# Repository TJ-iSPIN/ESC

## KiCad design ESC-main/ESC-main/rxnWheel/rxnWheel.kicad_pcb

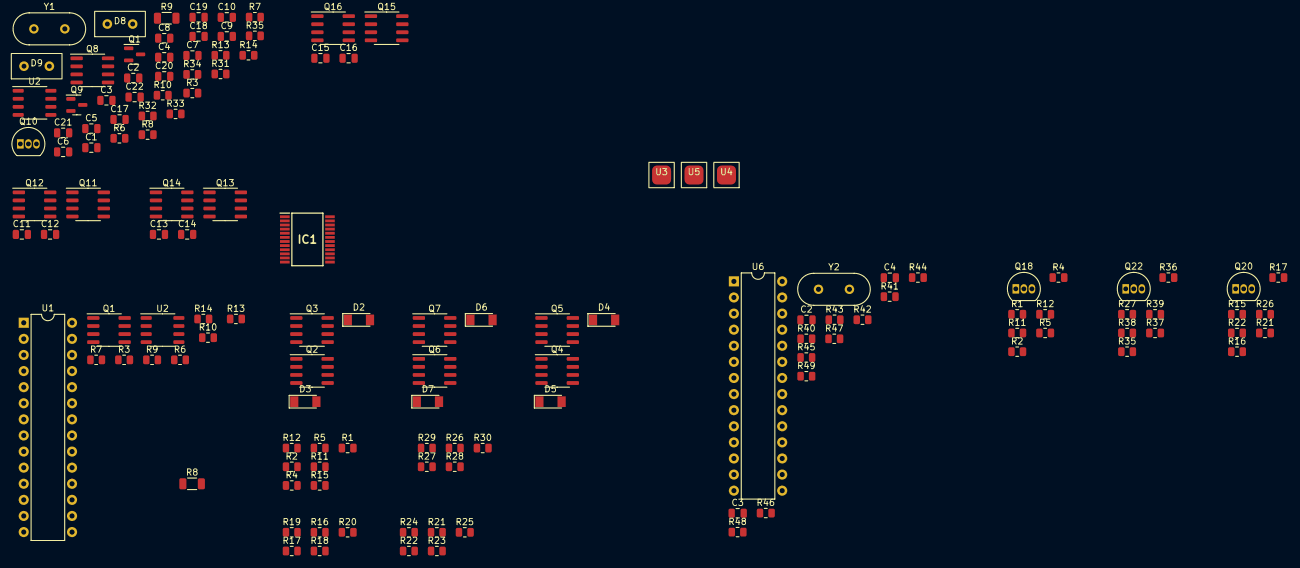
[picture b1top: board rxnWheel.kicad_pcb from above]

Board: 2 copper layers, 134 parts (0 on the bottom side), 73 nets, no tracks yet.

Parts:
C1, C3, C4#2, C8, C9, C10, C20, C21, C22: 1uF; C_0805_2012Metric
C2: 1nF; C_0805_2012Metric
C2#2, C3#2, C17, C18: 20pF; C_0805_2012Metric
C4: 0.47 uF; C_0805_2012Metric
C5, C7, C19: 0.1uF; C_0805_2012Metric
C6, C11, C12, C13, C14, C15, C16: 0.01uF; C_0805_2012Metric
D2, D3, D4, D5, D6, D7: BZV55B12; D_MiniMELF
D8: BPW20RF; 2x_jumper
D9: LED; 2x_jumper
IC1: TB9061AFNG; SOP65P760X160-24N
Q1, Q8: IRF7458; SOIC-8_3.9x4.9mm_P1.27mm
Q1#2, Q9: 2N7002; SOT-23
Q2, Q4, Q6, Q12, Q14, Q16: IRF7404; SOIC-8_3.9x4.9mm_P1.27mm
Q3, Q5, Q7, Q11, Q13, Q15: Si4162DY; SOIC-8_3.9x4.9mm_P1.27mm
Q10, Q18, Q20, Q22: 2N3904; TO-92_Inline
R1, R1#2, R2#2, R7, R15, R16, R16#2, R17#2, R21, R22, R26#2, R27, R27#2, R35#2: 100; R_0805_2012Metric
R2, R3, R3#2, R4, R4#2, R5, R5#2, R6, R6#2, R7#2, R8, R11#2, R12, R13, R13#2, R14, R17, R18, R19, R20, R21#2, R22#2, R23, R24, R25, R26, R28, R29, R30, R31, R36, R37, R38, R39, R40, R44, R45, R46: 10K; R_0805_2012Metric
R8#2, R9: 3m; R_1206_3216Metric
R9#2: 6K; R_0805_2012Metric
R10: 9.5K; R_0805_2012Metric
R10#2: 4K; R_0805_2012Metric
R11, R14#2: 3K; R_0805_2012Metric
R12#2: 7K; R_0805_2012Metric
R15#2, R32, R33, R34: 1K; R_0805_2012Metric
R35: 3m; R_0805_2012Metric
R41, R42, R43, R47, R48, R49: 33K; R_0805_2012Metric
U1, U6: ATmega328-P; DIP-28_W7.62mm
U2, U2#2: MAX4373F; SO-8_3.9x4.9mm_P1.27mm
U3, U4, U5: Pad
Y1, Y2: 16MHz; Crystal_HC49-4H_Vertical

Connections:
+5V: C1.1, C4#2.1, D8.1 (K), D9.2 (A), Q10.3 (C), Q18.3 (C), Q20.3 (C), Q22.3 (C), R13.2, R40.2, U1.7 (VCC), U1.20 (AVCC), U6.7 (VCC), U6.20 (AVCC)
+BATT: C19.1, Q1.1 (S), Q1.2 (S), Q1.3 (S), Q8.1 (S), Q8.2 (S), Q8.3 (S), R3.1, R3#2.1, R6.1, R8.1, U2.1 (Vcc)
/DRVR/A0: R43.1, R46.2, R49.2, U6.23 (PC0)
/DRVR/A1: R42.1, R45.2, R48.2, U6.24 (PC1)
/DRVR/A2: R41.1, R44.2, R47.2, U6.25 (PC2)
/U/BRK_OUT: C20.1, C22.1, Q12.5 (D), Q12.6 (D), Q12.7 (D), Q12.8 (D)
/V/BRK_OUT: C21.2, C22.2, Q16.5 (D), Q16.6 (D), Q16.7 (D), Q16.8 (D)
/W/BRK_OUT: C20.2, C21.1, Q14.5 (D), Q14.6 (D), Q14.7 (D), Q14.8 (D)
DRV_MTR: Q11.4 (G), Q12.4 (G), Q13.4 (G), Q14.4 (G), Q15.4 (G), Q16.4 (G)
GND: C1.2, C2.2, C2#2.1, C3.2, C3#2.1, C4.1, C4#2.2, C5.2, C6.1, C7.1, C8.2, C9.2, C10.2, C11.2, C13.2, C15.2, C17.1, C18.1, C19.2, D2.2 (A), D4.2 (A), D6.2 (A), IC1.2 (TEST), IC1.6 (SLA), IC1.7 (CW_CCW), IC1.9 (GND), Q1#2.2 (S), Q3.1 (S), Q3.2 (S), Q3.3 (S), Q5.1 (S), Q5.2 (S), Q5.3 (S), Q7.1 (S), Q7.2 (S), Q7.3 (S), R2.1, R4.2, R5.2, R5#2.2, R10#2.2, R11#2.2, R12.2, R12#2.2, R14.2, R14#2.2, R17.2, R18.2, R21#2.2, R22#2.2, R23.2, R26.2, R28.2, R31.1, R32.1, R33.1, R34.1, R35.1, R36.2, R37.2, R38.2, R39.2, R44.1, R45.1, R46.1, U1.8 (GND), U1.22 (GND), U2.4 (GND), U2#2.4 (GND), U6.8 (GND), U6.22 (GND)
I_MOTOR_TELEM: R9#2.1, R10.1, U1.23 (PC0), U2.2 (OUT), U2#2.2 (OUT)
I_SENSE: R4#2.1, R15#2.2, R35.2
MTR_FRQ: Q10.1 (E), R33.2, U1.16 (PB2)
MTR_V_TELEM: R13#2.2, R14.1
unnamed: C2.1, IC1.1 (PSIG), R1#2.2, R2.2
unnamed: C2#2.2, U6.9 (XTAL1/PB6), Y2.1
unnamed: C3.1, IC1.16 (VB)
unnamed: C3#2.2, Y2.2
unnamed: C4.2, IC1.3 (IPC)
unnamed: C6.2, IC1.21 (OCDET), R15#2.1
unnamed: C11.1, D2.1 (K), Q3.4 (G), Q18.1 (E), R12.1, R16.2, R18.1
unnamed: C12.2, D3.2 (A), Q2.4 (G), R11#2.1, R17#2.2, R19.2
unnamed: C13.1, D4.1 (K), Q5.4 (G), Q20.1 (E), R21.2, R23.1, R26.1
unnamed: C14.2, D5.2 (A), Q4.4 (G), R22.2, R22#2.1, R24.2
unnamed: C15.1, D6.1 (K), Q7.4 (G), Q22.1 (E), R26#2.2, R28.1, R39.1
unnamed: C16.2, D7.2 (A), Q6.4 (G), R27#2.2, R29.2, R38.1
unnamed: C17.2, U1.9 (XTAL1/PB6), Y1.1
unnamed: C18.2, Y1.2
unnamed: D8.2 (A), Q10.2 (B), R32.2
unnamed: D9.1 (K), R34.2
unnamed: Q1#2.3 (D), Q9.2 (S)
unnamed: Q1.4 (G), R3.2, R6#2.2, U2#2.6 (COUT1)
unnamed: Q1.5 (D), Q1.6 (D), Q1.7 (D), Q1.8 (D), R8#2.2, U2#2.8 (RS+)
unnamed: Q8.4 (G), Q9.3 (D), R3#2.2
unnamed: Q8.5 (D), Q8.6 (D), Q8.7 (D), Q8.8 (D), R9.2, U2.8 (RS+)
unnamed: Q9.1 (G), R6.2, U2.6 (COUT1)
unnamed: Q2.1 (S), Q2.2 (S), Q2.3 (S), Q3.5 (D), Q3.6 (D), Q3.7 (D), Q3.8 (D), Q11.5 (D), Q11.6 (D), Q11.7 (D), Q11.8 (D), R20.2
unnamed: Q4.1 (S), Q4.2 (S), Q4.3 (S), Q5.5 (D), Q5.6 (D), Q5.7 (D), Q5.8 (D), Q13.5 (D), Q13.6 (D), Q13.7 (D), Q13.8 (D), R25.2
unnamed: Q6.1 (S), Q6.2 (S), Q6.3 (S), Q7.5 (D), Q7.6 (D), Q7.7 (D), Q7.8 (D), Q15.5 (D), Q15.6 (D), Q15.7 (D), Q15.8 (D), R30.2
unnamed: R1.2, R4.1
unnamed: Q18.2 (B), R2#2.2, R5#2.1
unnamed: R15.2, R17.1
unnamed: Q20.2 (B), R16#2.2, R21#2.1
unnamed: R27.2, R36.1
unnamed: Q22.2 (B), R35#2.2, R37.1
unnamed: R6#2.1, R7#2.1, U2#2.1 (Vcc)
unnamed: R7.2, U1.15 (PB1)
unnamed: R9#2.2, R10#2.1, U2#2.3 (CIN1)
unnamed: R10.2, R14#2.1, U2.3 (CIN1)
unnamed: R40.1, U6.1 (~RESET/PC6)
unnamed: R41.2, R42.2, R43.2, U6.12 (PD6)
unnamed: R7#2.2, U2#2.5 (~RESET)
PWM_IN: R1#2.1, U1.11 (PD5)
RESET: R13.1, U1.1 (~RESET/PC6)
RSTMTRV: Q1#2.1 (G), U1.13 (PD7)
RSTMTRVOCP: R8.2, U1.12 (PD6), U2.5 (~RESET)
SFCF: IC1.5 (SFCF), R11.2, R12#2.1
SHUTOFF: IC1.4 (DIS), R31.2, U1.14 (PB0)
U_MTR: Q11.1 (S), Q11.2 (S), Q11.3 (S), Q12.1 (S), Q12.2 (S), Q12.3 (S), R47.1, U5.1 (V)
U_N: IC1.10 (OUTUN), R2#2.1, R16.1, U6.14 (PB0)
U_P: IC1.13 (OUTUP), R1.1, R17#2.1, U6.17 (PB3)
U_W: IC1.17 (WAVE_U), R20.1
VBUS: C8.1, C9.1, C10.1, C12.1, C14.1, C16.1, D3.1 (K), D5.1 (K), D7.1 (K), Q2.5 (D), Q2.6 (D), Q2.7 (D), Q2.8 (D), Q4.5 (D), Q4.6 (D), Q4.7 (D), Q4.8 (D), Q6.5 (D), Q6.6 (D), Q6.7 (D), Q6.8 (D), R8#2.1, R9.1, R13#2.1, R19.1, R24.1, R29.1, U2.7 (RS-), U2#2.7 (RS-)
VReg: C5.1, IC1.22 (ASIG), IC1.23 (VREG), IC1.24 (VDD), R11.1
V_MTR: Q15.1 (S), Q15.2 (S), Q15.3 (S), Q16.1 (S), Q16.2 (S), Q16.3 (S), R48.1, U3.1
V_N: IC1.11 (OUTVN), R16#2.1, R21.1, U6.15 (PB1)
V_P: IC1.14 (OUTVP), R15.1, R22.1, U6.18 (PB4)
V_W: IC1.18 (WAVE_V), R30.1
WAVE_CMP: C7.2, IC1.20 (WAVE_CMP), R4#2.2, R5.1
W_MTR: Q13.1 (S), Q13.2 (S), Q13.3 (S), Q14.1 (S), Q14.2 (S), Q14.3 (S), R49.1, U4.1
W_N: IC1.12 (OUTWN), R26#2.1, R35#2.1, U6.16 (PB2)
W_P: IC1.15 (OUTWP), R27.1, R27#2.1, U6.19 (PB5)
W_W: IC1.19 (WAVE_W), R25.1

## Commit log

2022-04-20 kiran changes
2022-04-22 Commit
    CoMmMMmMMMmits
2022-04-22 HANDS
    fix fix hands hands
2022-04-22 update gitignore
2022-04-22 remove backups
2022-04-22 minor changes
2022-04-23 Brake
    commmit
2022-04-23 LED
    led
2022-04-27 Bad push b/c im on a friends computer so i cnat use Git lol OK? but added atmega329 mtr driver but tbh theres a lot of issuse
    nah
2022-04-27 cleanup and corrections
2022-05-01 Cap
    Caps vbus --> gnd
2022-05-01 corrected capacitors
